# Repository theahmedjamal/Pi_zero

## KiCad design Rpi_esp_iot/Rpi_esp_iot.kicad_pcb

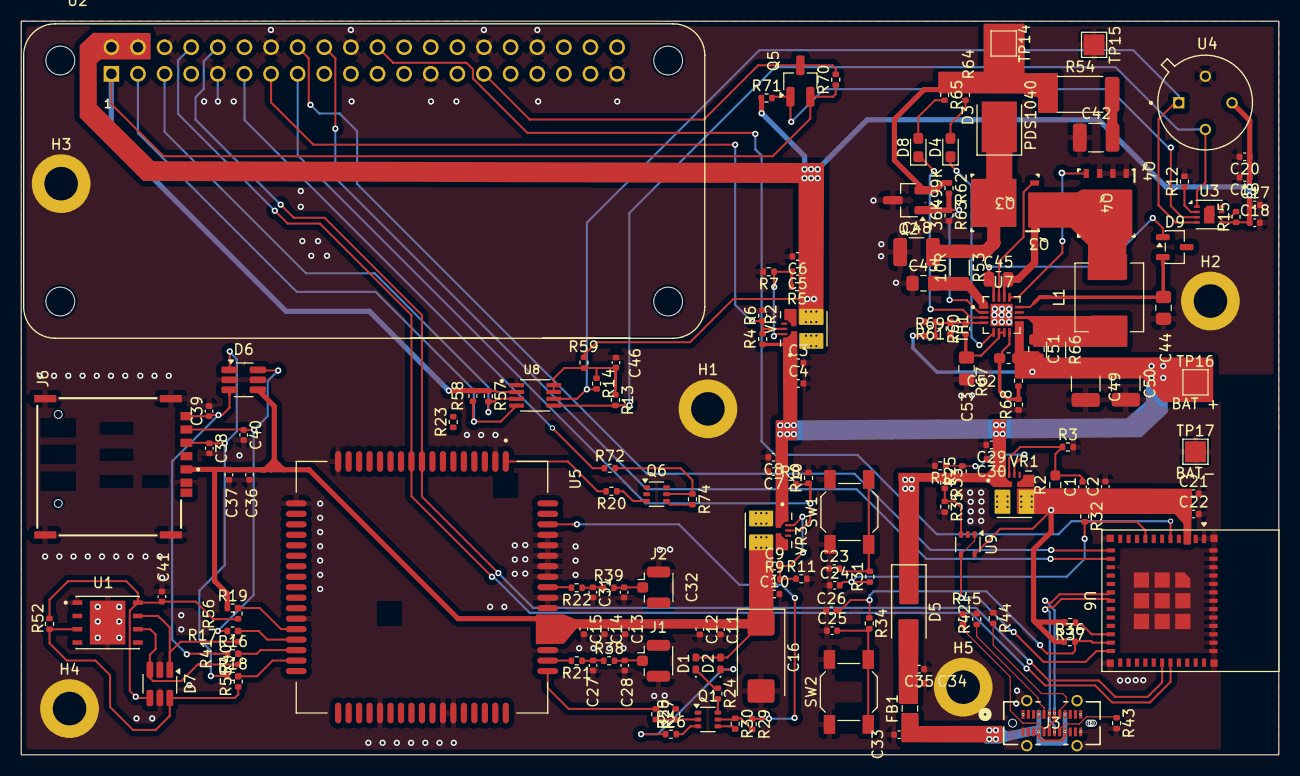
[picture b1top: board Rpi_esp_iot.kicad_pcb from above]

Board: 2 copper layers, 120.0 x 70.0 mm, 164 parts (0 on the bottom side), 92 nets.

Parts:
C1, C5, C9: 22pF; C_0402_1005Metric
C2, C6, C10: 33uF; C_0402_1005Metric
C3, C7, C29: 10uF; C_0402_1005Metric
C4, C8, C11, C12, C13, C14, C17, C19, C21, C23, C25, C27, C28, C30, C31, C32, C36, C37, C41: 100nF; C_0402_1005Metric
C15, C24, C26, C33, C34, C35: 1uF; C_0402_1005Metric
C16: 470uf; CP_EIA-7343-15_Kemet-W_HandSolder
C18, C20: 4.7uF; C_0402_1005Metric
C22, C38, C39, C40: 22uF; C_0402_1005Metric
C42: 2.2uF; C_1210_3225Metric_Pad1.33x2.70mm_HandSolder
C43, C44, C53: 1uF; C_0805_2012Metric_Pad1.18x1.45mm_HandSolder
C45, C51: 100nF; R_0805_2012Metric
C46: 1000pF; C_0402_1005Metric
C48, C49: 10uF; C_1210_3225Metric_Pad1.33x2.70mm_HandSolder
C50: 4.7uF; C_1210_3225Metric_Pad1.33x2.70mm_HandSolder
C52: 22pF; C_0603_1608Metric_Pad1.08x0.95mm_HandSolder
D1: XL-1005SURC; LED_0402_1005Metric_Pad0.77x0.64mm_HandSolder
D2: XL-1005UGC; LED_0402_1005Metric_Pad0.77x0.64mm_HandSolder
D3: PDS1040; D_PowerDI-5
D4, D8: LTST-C190GKT; LED_0603_1608Metric_Pad1.05x0.95mm_HandSolder
D5: SS26; D_SMA_Handsoldering
D6, D7: ESDA6V1BC6; SOT-23-6_Handsoldering
D9: BAT54C; SOT-23-3
FB1: MI0805K601R-10; C_0805_2012Metric
H1, H2, H3, H4, H5: MountingHole_Pad; MountingHole_3.2mm_M3_DIN965_Pad
J1, J2: Conn_01x03; U.FL_Hirose_U.FL-R-SMT-1_Vertical
J3: USB_C_Receptacle_USB2.0_16P; USB4115-03-C_GCT
J6: SIM8066-6-1-14-01-A_REVA; GCT_SIM8066-6-1-14-01-A_REVA
L1: 10uH; L_Vishay_IHLP-2525
Q1, Q6: MMDT3904; SOT-363_SC-70-6
Q2, Q5: NMOS; SOT-23_Handsoldering
Q3, Q4: CSD18540Q5B
R1, R6, R10, R12, R13, R14, R15, R32, R36, R37, R57, R58, R64, R65, R70, R71: 10K; R_0402_1005Metric
R2: 135K; R_0603_1608Metric_Pad0.98x0.95mm_HandSolder
R3, R7, R11: 30K; R_0402_1005Metric
R4, R8, R25: 48.7K; R_0402_1005Metric
R5: 220K; R_0402_1005Metric
R9: 165K; R_0402_1005Metric
R16, R17, R18, R19, R20, R21, R22, R23, R31, R34, R38, R39, R40, R41, R44, R45, R55, R56: 0R; R_0402_1005Metric
R24: 330R; R_0402_1005Metric
R26: 120R; R_0402_1005Metric
R27, R29, R72: 4.7K; R_0402_1005Metric
R28, R30, R74: 47K; R_0402_1005Metric
R33, R35: 24K; R_0402_1005Metric
R42, R43: 5.1K; R_0402_1005Metric
R52: 20k; R_0402_1005Metric
R53: 10R; R_1206_3216Metric_Pad1.30x1.75mm_HandSolder
R54: 2R; R_2512_6332Metric_Pad1.40x3.35mm_HandSolder
R59: 200K; R_0402_1005Metric
R60, R69: 5.23K; R_0402_1005Metric
R61: 30.1K; R_0402_1005Metric
R62, R67: 499K; R_0402_1005Metric
R63: 36K; R_0402_1005Metric
R66: 20mR; R_1206_3216Metric_Pad1.30x1.75mm_HandSolder
R68: 100K; R_0402_1005Metric
SW1, SW2: SW_SPST; SW_SPST_SKQG_WithStem
TH1: Thermistor_NTC; R_0402_1005Metric_Pad0.72x0.64mm_HandSolder
TP14, TP15: TestPoint; TestPoint_Pad_2.0x2.0mm
TP16: BAT +; TestPoint_Pad_2.0x2.0mm
TP17: BAT-; TestPoint_Pad_2.0x2.0mm
U1: ST4SI2M0020TPIFW; SON127P500X600X100-9N
U2: RASPBERRYPI-ZERO; RASPBERRYPI-ZERO_RPI-ZERO
U3: SHT30-DIS; Sensirion_DFN-8-1EP_2.5x2.5mm_P0.5mm_EP1.1x1.7mm
U4: MLX90614ESF-AAA-000-TU-ND; TO254P942H425-4
U5: SIM7070G; MODULE_SIM7070G
U6: ESP32-C6-MINI-1
U7: BQ24650RVAT; QFN50P350X350X100-17N
U8: PCA9306DCTR; SOP65P400X130-8N
U9: MCP6001x-LT; SOT-353_SC-70-5
VR1, VR2, VR3: TPSM863252RDXR; VREG_TPSM863252RDXR

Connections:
+3.3V_ESP: C1.1, C2.1, C21.1, C22.1, R2.1, R32.1, R36.1, R37.2, U6.3 (3V3), U9.5 (V+), VR1.3 (VOUT)
+3V3_RPI: Q5.2 (G), R57.1, R58.1, R70.1, U2.1 (3V3[1]), U8.2 (VREF1)
+5V_RPi: C5.1, C6.1, C17.1, C18.1, C19.1, C20.1, R5.1, R15.1, R59.1, R71.1, U2.2 (5V[1]), U2.4 (5V[2]), U3.5 (VDD), U4.3 (VDD), VR2.3 (VOUT)
+Vbat: C3.1, C4.1, C7.1, C8.1, C29.1, C30.1, C49.2, C50.1, C51.2, C52.1, D5.1 (K), R4.1, R8.1, R25.1, R33.1, R66.2, R67.2, R69.1, TP16.1, U7.9 (SRN), VR1.1 (VIN), VR2.1 (VIN), VR3.1 (VIN)
BATTERY: U6.24 (IO18), U9.1, U9.4 (-)
BAT_TEMP: R60.2, R61.1, R69.2, TH1.1, U7.4 (TS)
ESIM_CLK: D7.3 (TVS2), R40.1, U1.6 (CLK)
ESIM_DATA: D7.6 (TVS4), R52.2, R55.1, U1.3 (I/O)
ESIM_RST: D7.1 (TVS1), R41.1, U1.7 (~RESET)
ESIM_VCC: C41.2, D7.4 (TVS3), R52.1, R56.1, U1.8 (VCC)
ESP_BOOT: C26.2, R34.1, R36.2, U6.23 (IO9)
ESP_EN: C24.2, R31.1, R32.2, U6.8 (EN)
ESP_GPIO0: U2.16 (GEN4/GPIO23), U6.12 (IO0)
ESP_GPIO1: U2.18 (GEN5/GPIO24), U6.13 (IO1)
ESP_GPIO2: U2.22 (GEN/6GPIO25), U6.5 (IO2)
ESP_GPIO8: R37.1, U6.22 (IO8)
ESP_RX: U2.10 (RXD0/GPIO15), U5.9 (UART1_TXD), U6.30 (RXD0)
ESP_TX: U2.8 (TXD0/GPIO14), U5.10 (UART1_RXD), U6.31 (TXD0)
ESP_USB_D_N: J3.A7 (D-), J3.B7 (D-), U6.17 (IO12)
ESP_USB_D_P: J3.A6 (D+), J3.B6 (D+), U6.18 (IO13)
GND: C2.2, C3.2, C4.2, C6.2, C7.2, C8.2, C10.2, C11.2, C12.2, C13.2, C14.2, C15.2, C16.2, C17.2, C18.2, C19.2, C20.2, C21.2, C22.2, C23.1, C24.1, C25.1, C26.1, C27.2, C28.2, C29.2, C30.2, C31.2, C32.2, C33.1, C34.1, C35.1, C36.2, C37.2, C38.2, C39.2, C40.2, C41.1, C42.1, C43.1, C44.1, C46.1, C48.1, C49.1, C50.2, C53.2, D6.2 (COM), D6.5 (COM), D7.2 (COM), D7.5 (COM), H1.1, H2.1, H3.1, H4.1, H5.1, J1.2, J2.2, J3.A1 (GND), J3.A12 (GND), J3.B1 (GND), J3.B12 (GND), J6.C5 (GND), J6.G1 (GND), J6.G2 (GND), J6.G3 (GND), J6.G4 (GND), Q2.3 (S), Q4.3, R1.2, R3.2, R6.2, R7.2, R10.2, R11.2, R12.2, R35.2, R42.2, R43.2, R44.1, R45.1, R61.2, R63.2, R68.1, SW1.1 (A), SW2.1 (A), TH1.2, TP15.1, TP17.1, U1.1 (GND), U1.9 (EXP), U2.6 (GND[8]), U2.9 (GND[1]), U2.14 (GND[4]), U2.20 (GND[5]), U2.25 (GND[2]), U2.30 (GND[6]), U2.34 (GND[7]), U2.39 (GND[3]), U3.7 (R), U3.8 (VSS), U3.9 (VSS), U4.4 (VSS), U5.2 (GND), U5.17 (GND), U5.18 (GND), U5.29 (GND), U5.39 (GND), U5.45 (GND), U5.46 (GND), U5.54 (GND), U5.58 (GND), U5.59 (GND), U5.61 (GND), U5.62 (GND), U5.63 (GND), U5.64 (GND), U5.65 (GND), U6.1 (GND), U6.2 (GND), U6.11 (GND), U6.14 (GND), U6.36 (GND), U6.37 (GND), U6.38 (GND), U6.39 (GND), U6.40 (GND), U6.41 (GND), U6.42 (GND), U6.43 (GND), U6.44 (GND), U6.45 (GND), U6.46 (GND), U6.47 (GND), U6.48 (GND), U6.49 (GND), U6.50 (GND), U6.51 (GND), U6.52 (GND), U6.53 (GND), U7.11 (GND), U7.17 (EPAD), U8.1 (GND), U9.2 (V-), VR1.4 (PGND), VR2.4 (PGND), VR3.4 (PGND)
GNSS_ANT: C27.1, R21.1, R38.1
NETLIGHT: R27.1, U5.52 (NETLIGHT)
unnamed: C33.2, FB1.1, J3.A4 (VBUS), J3.A9 (VBUS), J3.B4 (VBUS), J3.B9 (VBUS)
unnamed: C42.2, R54.2
unnamed: D1.1 (K), R24.1
unnamed: D2.1 (K), R26.1
unnamed: C48.2, D3.1 (K), Q3.1, R53.1
unnamed: D4.2 (A), R64.2
unnamed: D4.1 (K), U7.5 (STAT2)
unnamed: C34.2, C35.2, D5.2 (A), FB1.2
unnamed: D8.2 (A), R65.2
unnamed: D8.1 (K), U7.3 (STAT1)
unnamed: C44.2, D9.2 (A), U7.12 (REGN)
unnamed: C45.1, D9.1 (K), U7.16 (BTST)
unnamed: C28.1, J1.1, R38.2
unnamed: C32.1, J2.1, R39.2
unnamed: J3.A5 (CC1), R42.1
unnamed: J3.B5 (CC2), R43.1
unnamed: J3.A8 (SBU1), R44.2
unnamed: J3.B8 (SBU2), R45.2
unnamed: Q1.2 (B1), R27.2, R28.1
unnamed: Q1.6 (C1), R24.2
unnamed: Q1.1 (E1), R28.2
unnamed: Q1.5 (B2), R29.2, R30.1
unnamed: Q1.3 (C2), R26.2
unnamed: Q1.4 (E2), R30.2
unnamed: Q2.1 (D), R62.2, R63.1, U7.2 (MPPSET)
unnamed: Q6.5 (B2), R72.2, R74.1
unnamed: Q6.4 (E2), R74.2
unnamed: C23.2, R31.2, SW1.2 (B)
unnamed: C25.2, R34.2, SW2.2 (B)
unnamed: R12.1, U3.2 (ADDR)
unnamed: R15.2, U3.6 (~RESET)
unnamed: R23.1, U5.6 (BOOT_CFG)
unnamed: R21.2, U5.53 (GNSS_ANT)
unnamed: R20.2, U5.1 (PWRKEY)
unnamed: R22.2, U5.60 (RF_ANT)
unnamed: R16.2, R40.2, U5.32 (SIM_CLK)
unnamed: R17.2, R41.2, U5.31 (SIM_DATA)
unnamed: R18.2, R55.2, U5.33 (SIM_RST)
unnamed: R19.2, R56.2, U5.30 (SIM_VDD)
unnamed: Q3.2, U7.15 (HIDRV)
unnamed: Q4.2, U7.13 (LODRV)
unnamed: C45.2, L1.1, Q3.3, Q4.1, U7.14 (PH)
unnamed: C51.1, L1.2, R66.1, U7.10 (SRP)
unnamed: C53.1, R60.1, U7.6 (VREF), U7.7 (TERM_EN)
unnamed: C43.2, R53.2, U7.1 (VCC)
unnamed: C52.2, R67.1, R68.2, U7.8 (VFB)
unnamed: C46.2, R13.1, R14.1, R59.2, U8.7 (VREF2), U8.8 (EN)
unnamed: R33.2, R35.1, U9.3 (+)
unnamed: R1.1, R25.2, VR1.6 (EN)
unnamed: C1.2, R2.2, R3.1, VR1.7 (FB)
unnamed: C5.2, R5.2, R7.1, VR2.7 (FB)
unnamed: C9.2, R9.2, R11.1, VR3.7 (FB)
RF_ANT: C31.1, R22.1, R39.1
RPI_PWR_EN: R4.2, R6.1, U2.13 (GPIO27/GEN2), VR2.6 (EN)
RPI_SCL: R57.2, U2.5 (GPIO3/SCL), U8.3 (SCL1)
RPI_SDA: R58.2, U2.3 (GPIO2/SDA), U8.4 (SDA1)
SHT_ALT: Q5.1 (D), R71.2, U3.3 (ALERT)
SHT_ALT_Rpi: Q5.3 (S), R70.2, U2.29 (GPIO5)
SIM_CLK: C39.1, D6.3 (TVS2), J6.C3 (CLK), R16.1
SIM_DATA: C40.1, D6.6 (TVS4), J6.C7 (I/O), R17.1
SIM_PWRKEY: Q6.3 (C2), R20.1
SIM_PWRKEY_Rpi: R72.1, U2.11 (GPIO17/GEN0)
SIM_PWR_EN: R8.2, R10.1, U2.15 (GPIO22/GEN3), VR3.6 (EN)
SIM_RST: C38.1, D6.1 (TVS1), J6.C2 (RST), R18.1
SIM_VCC: C9.1, C10.1, C11.1, C12.1, C13.1, C14.1, C15.1, C16.1, C36.1, C37.1, D1.2 (A), D2.2 (A), D6.4 (TVS3), J6.C1 (VCC), R9.1, R19.1, U5.55 (VBAT), U5.56 (VBAT), U5.57 (VBAT), VR3.3 (VOUT)
SNS_I2C_SCL: R14.2, U3.4 (SCL), U4.1 (SCL/VZ), U8.6 (SCL2)
SNS_I2C_SDA: R13.2, U3.1 (SDA), U4.2 (SDA/PWM), U8.5 (SDA2)
STATUS: R29.1, U5.66 (STATUS)
VIN: D3.2 (A), Q2.2 (G), R54.1, R62.1, R64.1, R65.1, TP14.1

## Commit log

2026-04-01 Initial commit: Schematic files are added
2026-04-05 Add eSIM connections and reorganize schematic layout
2026-04-05 Level shifter is replaced to PCA9360 i2c bus dedicated
2026-04-06 Solar Charge Controller added and layout is improved
2026-04-07 Sourcing Complete + Added all Components to PCB + Resolved errors
2026-04-17 Placement by usama
2026-04-28 Complete Placement + Partial modification in Schematic(Sim+simreset+Power Connection wit diode
2026-05-01 Routing Complete
